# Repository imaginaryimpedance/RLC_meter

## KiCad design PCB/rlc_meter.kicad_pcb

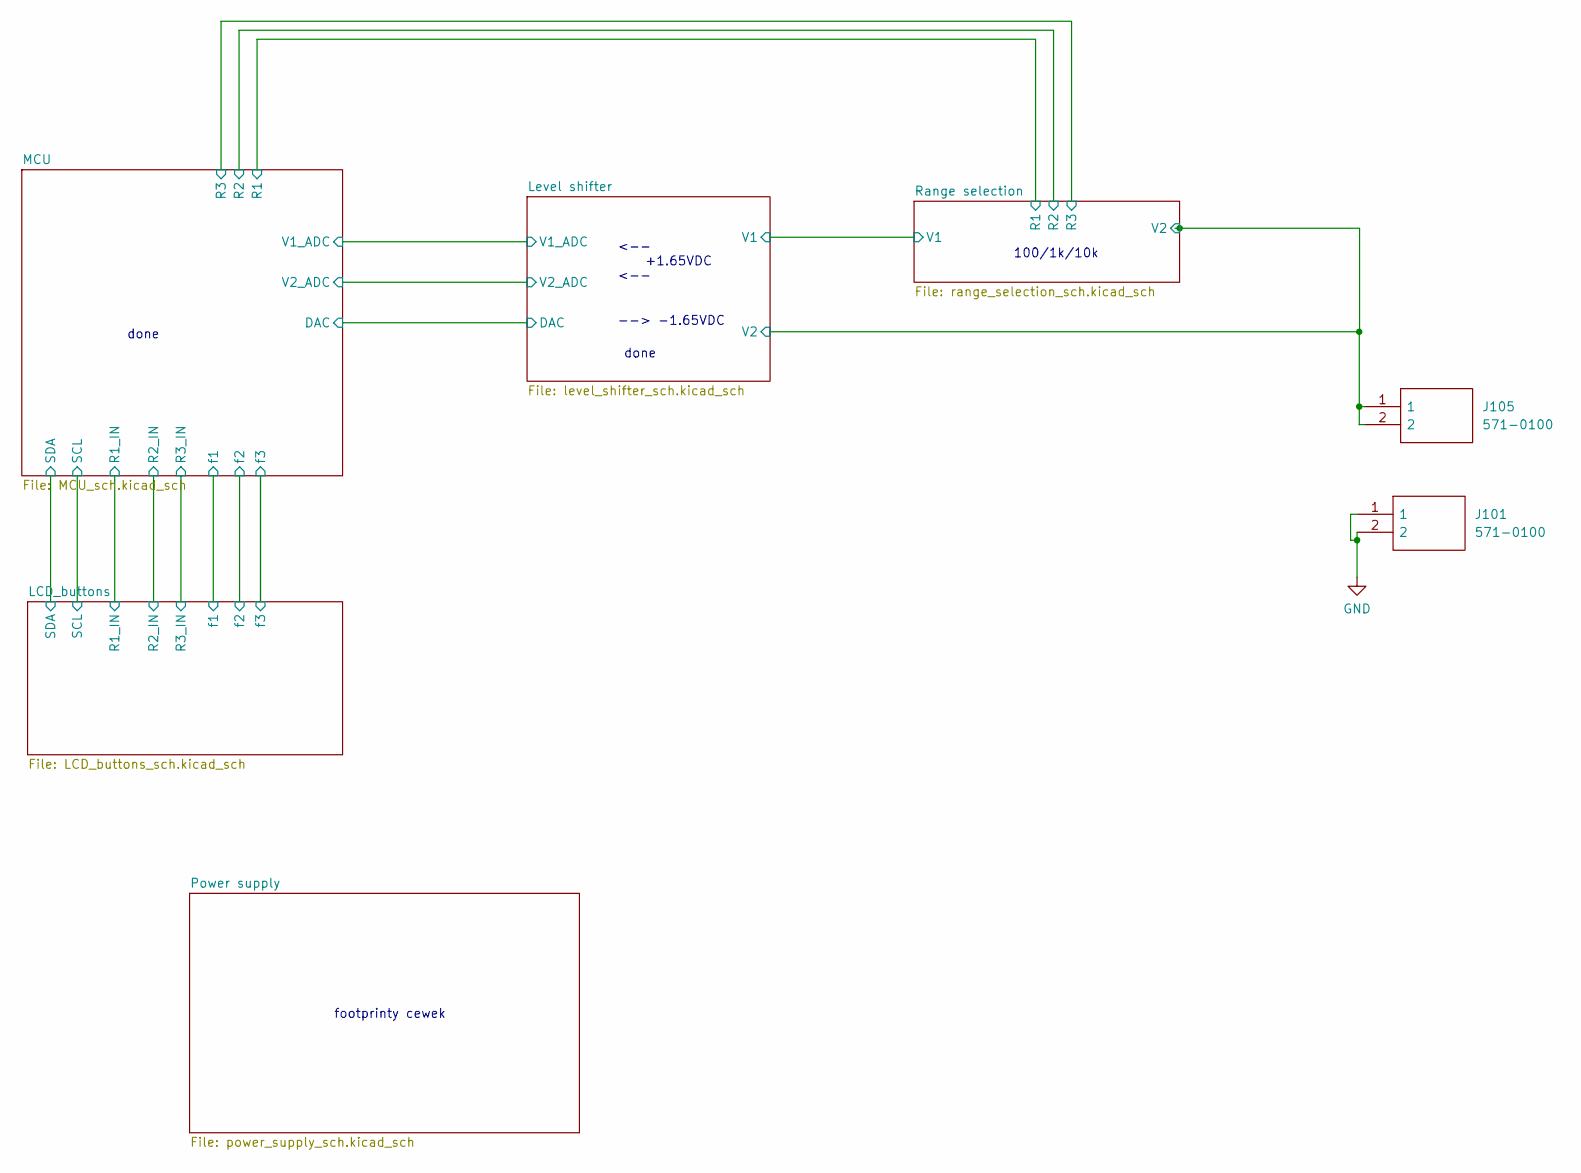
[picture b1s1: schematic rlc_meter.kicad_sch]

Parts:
J101, J105: 571-0100; 5710100; Manufacturer_Part_Number 571-0100; Mouser Part Number 164-6218

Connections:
/Level shifter/V2: J105.1, J105.2; also elsewhere on the board
GND: J101.1, J101.2; also elsewhere on the board

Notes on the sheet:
100/1k/10k
<-- +1.65VDC <--
footprinty cewek
done
--> -1.65VDC

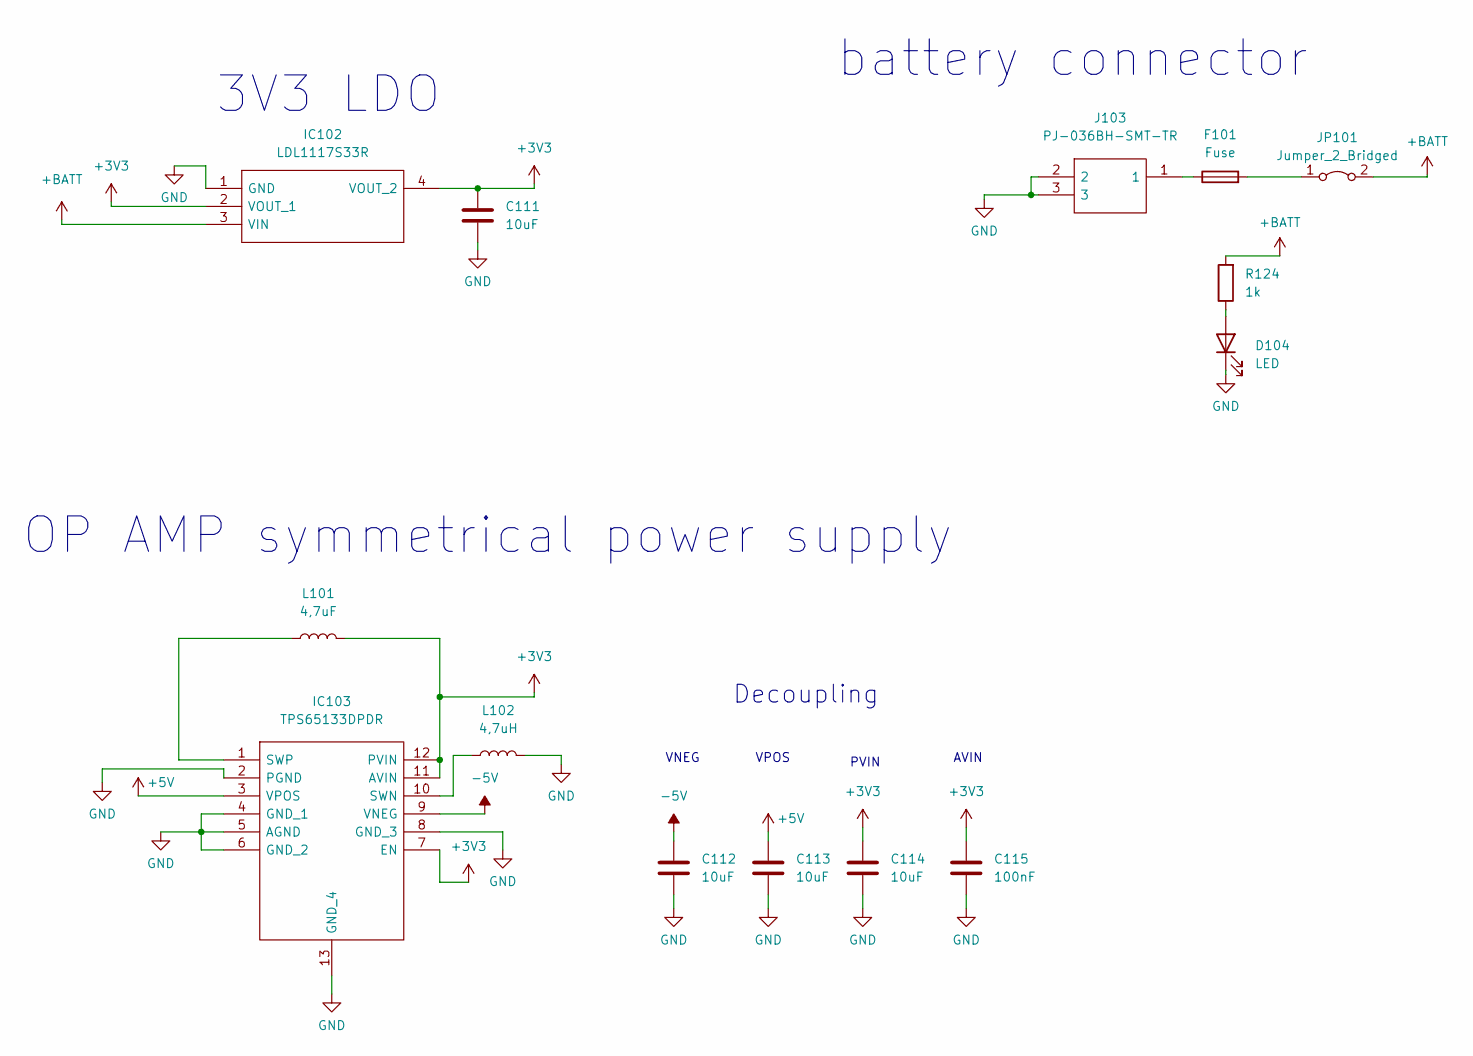
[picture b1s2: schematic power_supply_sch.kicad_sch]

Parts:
C111, C112, C113, C114: 10uF; C_1206_3216Metric
C115: 100nF; C_1206_3216Metric
D104: LED; LED_1206_3216Metric
F101: Fuse; Fuse_1206_3216Metric
IC102: LDL1117S33R; SOT230P700X180-4N; Manufacturer_Part_Number LDL1117S33R; Mouser Part Number 511-LDL1117S33R
IC103: TPS65133DPDR; SON45P300X300X80-13N-D; Manufacturer_Part_Number TPS65133DPDR; Mouser Part Number 595-TPS65133DPDR
J103: PJ-036BH-SMT-TR; PJ036BHSMTTR; Manufacturer_Part_Number PJ-036BH-SMT-TR; Mouser Part Number 490-PJ-036BH-SMT-TR
JP101: Jumper_2_Bridged; PinHeader_1x02_P2.54mm_Vertical_SMD_Pin1Right
L101: 4,7uF; 744031004
L102: 4,7uH; 744031004
R124: 1k; R_1206_3216Metric

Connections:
+3V3: C111.1, C114.1, C115.1, IC102.2 (VOUT_1), IC102.4 (VOUT_2), IC103.7 (EN), IC103.11 (AVIN), IC103.12 (PVIN), L101.2; also elsewhere on the board
+5V: C113.1, IC103.3 (VPOS); also elsewhere on the board
+BATT: IC102.3 (VIN), JP101.2 (B), R124.2
-5V: C112.1, IC103.9 (VNEG); also elsewhere on the board
GND: C111.2, C112.2, C113.2, C114.2, C115.2, D104.1 (K), IC102.1 (GND), IC103.2 (PGND), IC103.4 (GND_1), IC103.5 (AGND), IC103.6 (GND_2), IC103.8 (GND_3), IC103.13 (GND_4), J103.2, J103.3, L102.2; also elsewhere on the board
unnamed: D104.2 (A), R124.1
unnamed: F101.1, J103.1
unnamed: F101.2, JP101.1 (A)
unnamed: IC103.1 (SWP), L101.1
unnamed: IC103.10 (SWN), L102.1

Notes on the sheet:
battery connector
3V3 LDO
VPOS
PVIN
OP AMP symmetrical power supply
AVIN
Decoupling
VNEG

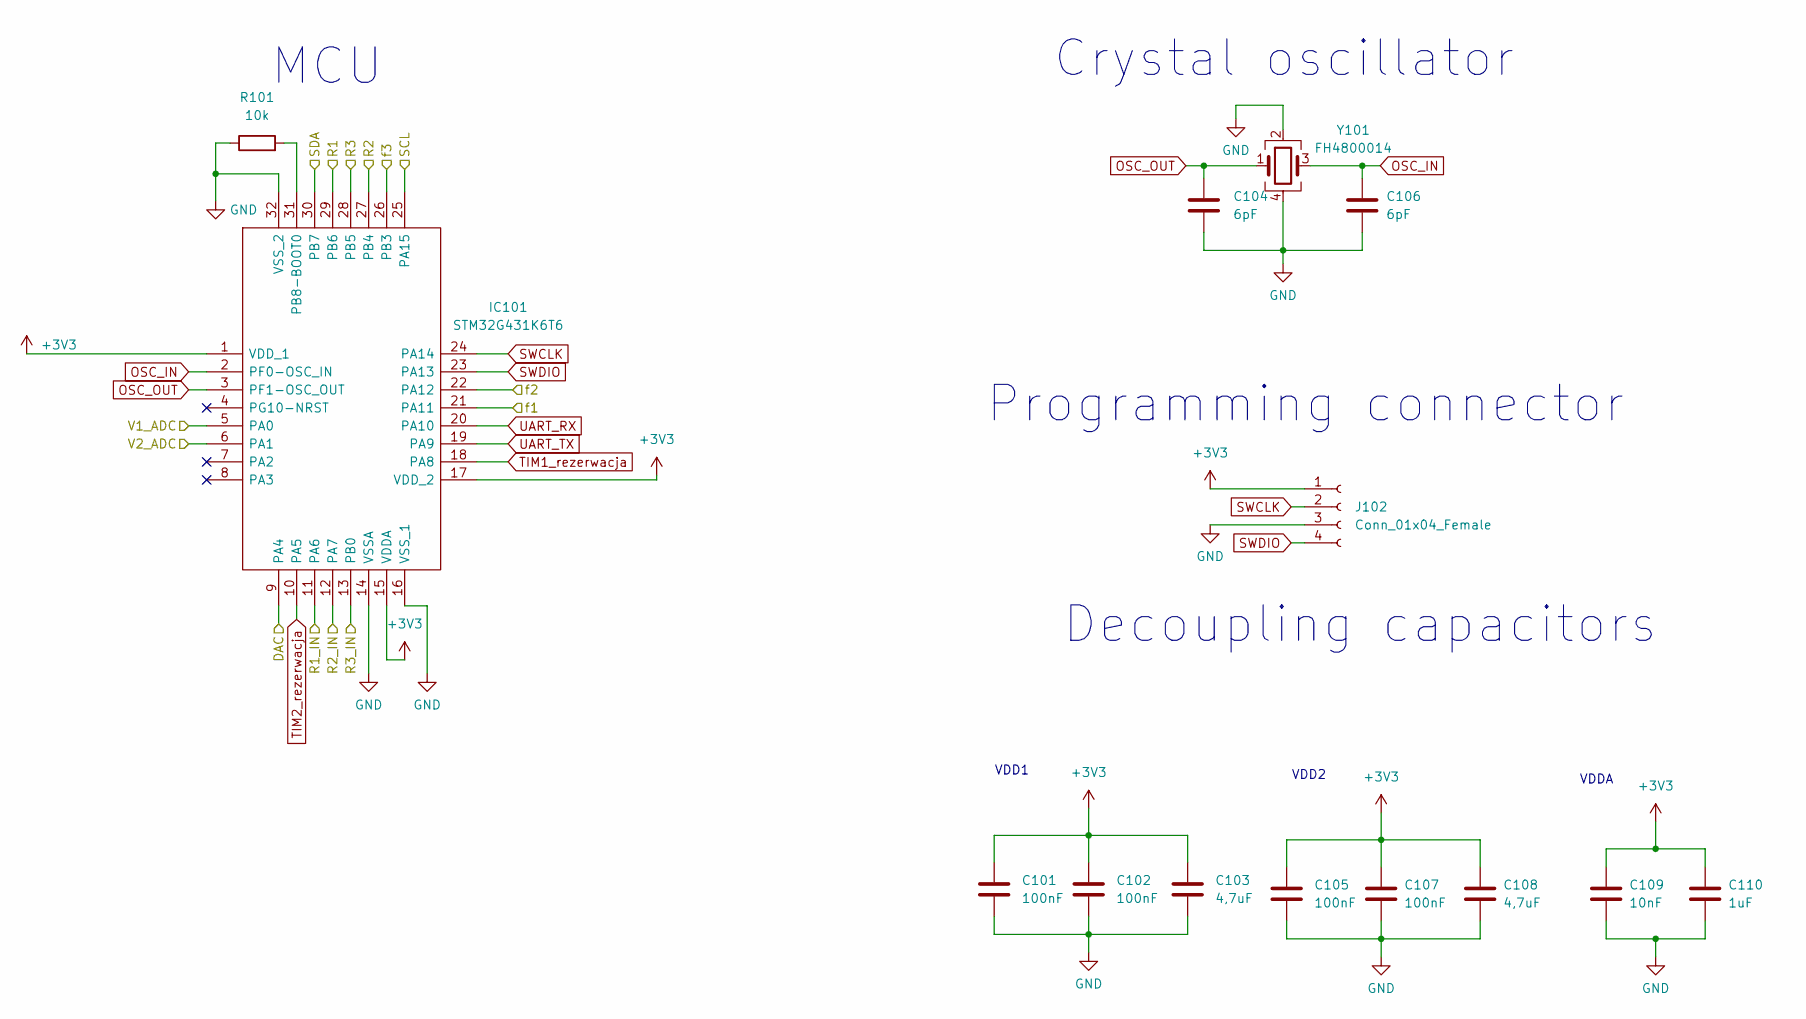
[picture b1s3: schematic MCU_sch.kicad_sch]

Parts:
C101, C102, C105, C107: 100nF; C_1206_3216Metric
C103, C108: 4,7uF; C_1206_3216Metric
C104, C106: 6pF; C_1206_3216Metric
C109: 10nF; C_1206_3216Metric
C110: 1uF; C_1206_3216Metric
IC101: STM32G431K6T6; QFP80P900X900X160-32N; Manufacturer_Part_Number STM32G431K6T6; Mouser Part Number 511-STM32G431K6T6
J102: Conn_01x04_Female; PinHeader_1x04_P2.54mm_Vertical_SMD_Pin1Left
R101: 10k; R_1206_3216Metric
Y101: FH4800014

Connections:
+3V3: C101.1, C102.1, C103.1, C105.1, C107.1, C108.1, C109.1, C110.1, IC101.1 (VDD_1), IC101.15 (VDDA), IC101.17 (VDD_2), J102.1; also elsewhere on the board
/LCD_buttons/R1_IN: IC101.11 (PA6); also elsewhere on the board
/LCD_buttons/R2_IN: IC101.12 (PA7); also elsewhere on the board
/LCD_buttons/R3_IN: IC101.13 (PB0); also elsewhere on the board
/LCD_buttons/SCL: IC101.25 (PA15); also elsewhere on the board
/LCD_buttons/SDA: IC101.30 (PB7); also elsewhere on the board
/LCD_buttons/f1: IC101.21 (PA11); also elsewhere on the board
/LCD_buttons/f2: IC101.22 (PA12); also elsewhere on the board
/LCD_buttons/f3: IC101.26 (PB3); also elsewhere on the board
/Level shifter/DAC: IC101.9 (PA4); also elsewhere on the board
/Level shifter/V1_ADC: IC101.5 (PA0); also elsewhere on the board
/Level shifter/V2_ADC: IC101.6 (PA1); also elsewhere on the board
/MCU/R1: IC101.29 (PB6); also elsewhere on the board
/MCU/R2: IC101.27 (PB4); also elsewhere on the board
/MCU/R3: IC101.28 (PB5); also elsewhere on the board
GND: C101.2, C102.2, C103.2, C104.2, C105.2, C106.2, C107.2, C108.2, C109.2, C110.2, IC101.14 (VSSA), IC101.16 (VSS_1), IC101.32 (VSS_2), J102.3, R101.1, Y101.2, Y101.4; also elsewhere on the board
unnamed: IC101.31 (PB8-BOOT0), R101.2
OSC_IN: C106.1, IC101.2 (PF0-OSC_IN), Y101.3
OSC_OUT: C104.1, IC101.3 (PF1-OSC_OUT), Y101.1
SWCLK: IC101.24 (PA14), J102.2
SWDIO: IC101.23 (PA13), J102.4
TIM1_rezerwacja: IC101.18 (PA8)
TIM2_rezerwacja: IC101.10 (PA5)
UART_RX: IC101.20 (PA10)
UART_TX: IC101.19 (PA9)

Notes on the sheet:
VDD2
MCU
VDD1
VDDA
Decoupling capacitors
Crystal oscillator
Programming connector

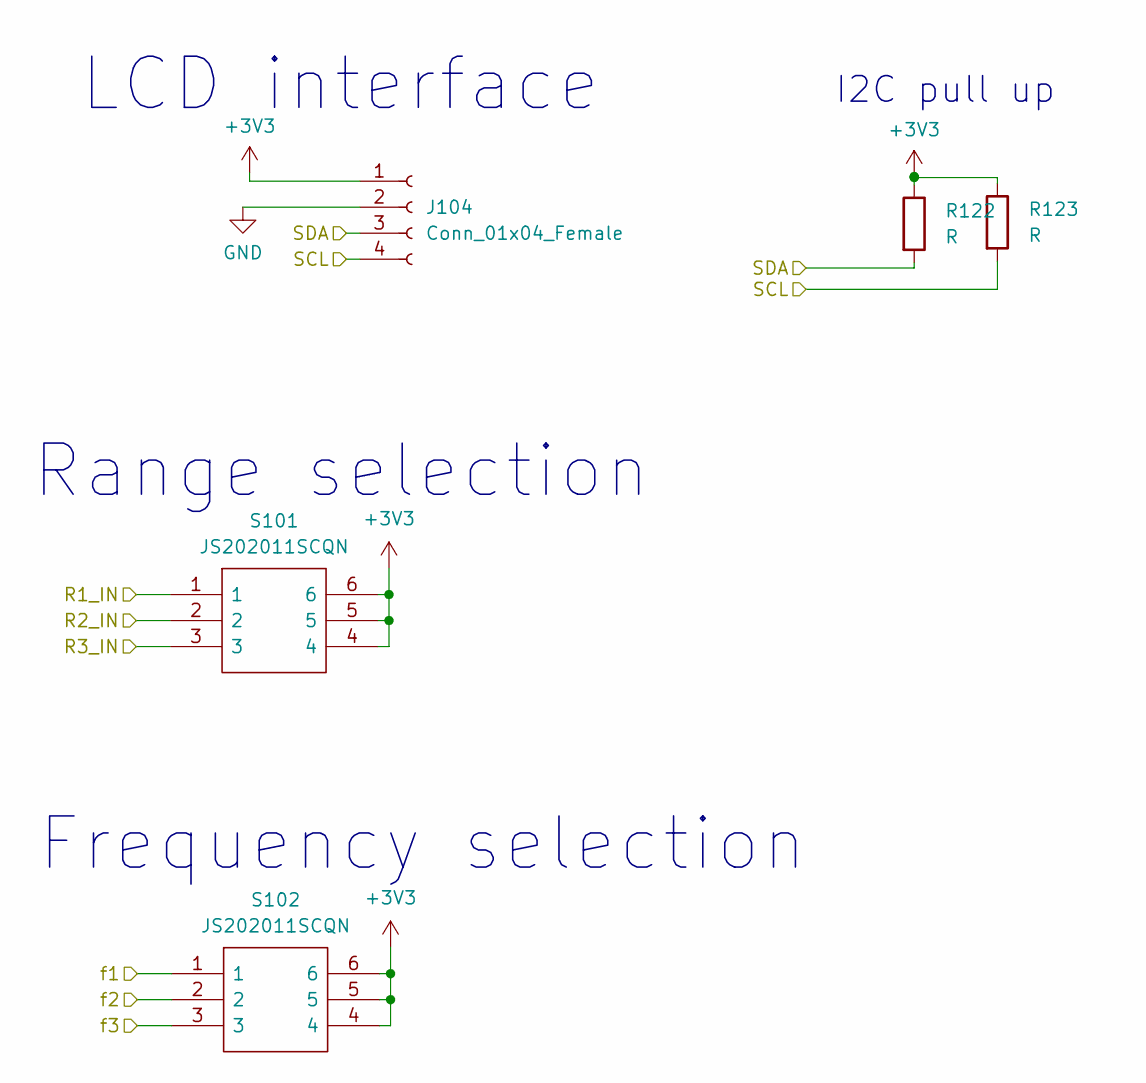
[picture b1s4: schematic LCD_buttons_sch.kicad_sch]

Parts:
J104: Conn_01x04_Female; PinHeader_1x04_P2.54mm_Vertical_SMD_Pin1Left
R122, R123: R; R_1206_3216Metric
S101, S102: JS202011SCQN; Manufacturer_Part_Number JS202011SCQN; Mouser Part Number 611-JS202011SCQN

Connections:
+3V3: J104.1, R122.1, R123.1, S101.4, S101.5, S101.6, S102.4, S102.5, S102.6; also elsewhere on the board
/LCD_buttons/R1_IN: S101.1; also elsewhere on the board
/LCD_buttons/R2_IN: S101.2; also elsewhere on the board
/LCD_buttons/R3_IN: S101.3; also elsewhere on the board
/LCD_buttons/SCL: J104.4, R123.2; also elsewhere on the board
/LCD_buttons/SDA: J104.3, R122.2; also elsewhere on the board
/LCD_buttons/f1: S102.1; also elsewhere on the board
/LCD_buttons/f2: S102.2; also elsewhere on the board
/LCD_buttons/f3: S102.3; also elsewhere on the board
GND: J104.2; also elsewhere on the board

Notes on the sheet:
I2C pull up
LCD interface
Frequency selection
Range selection

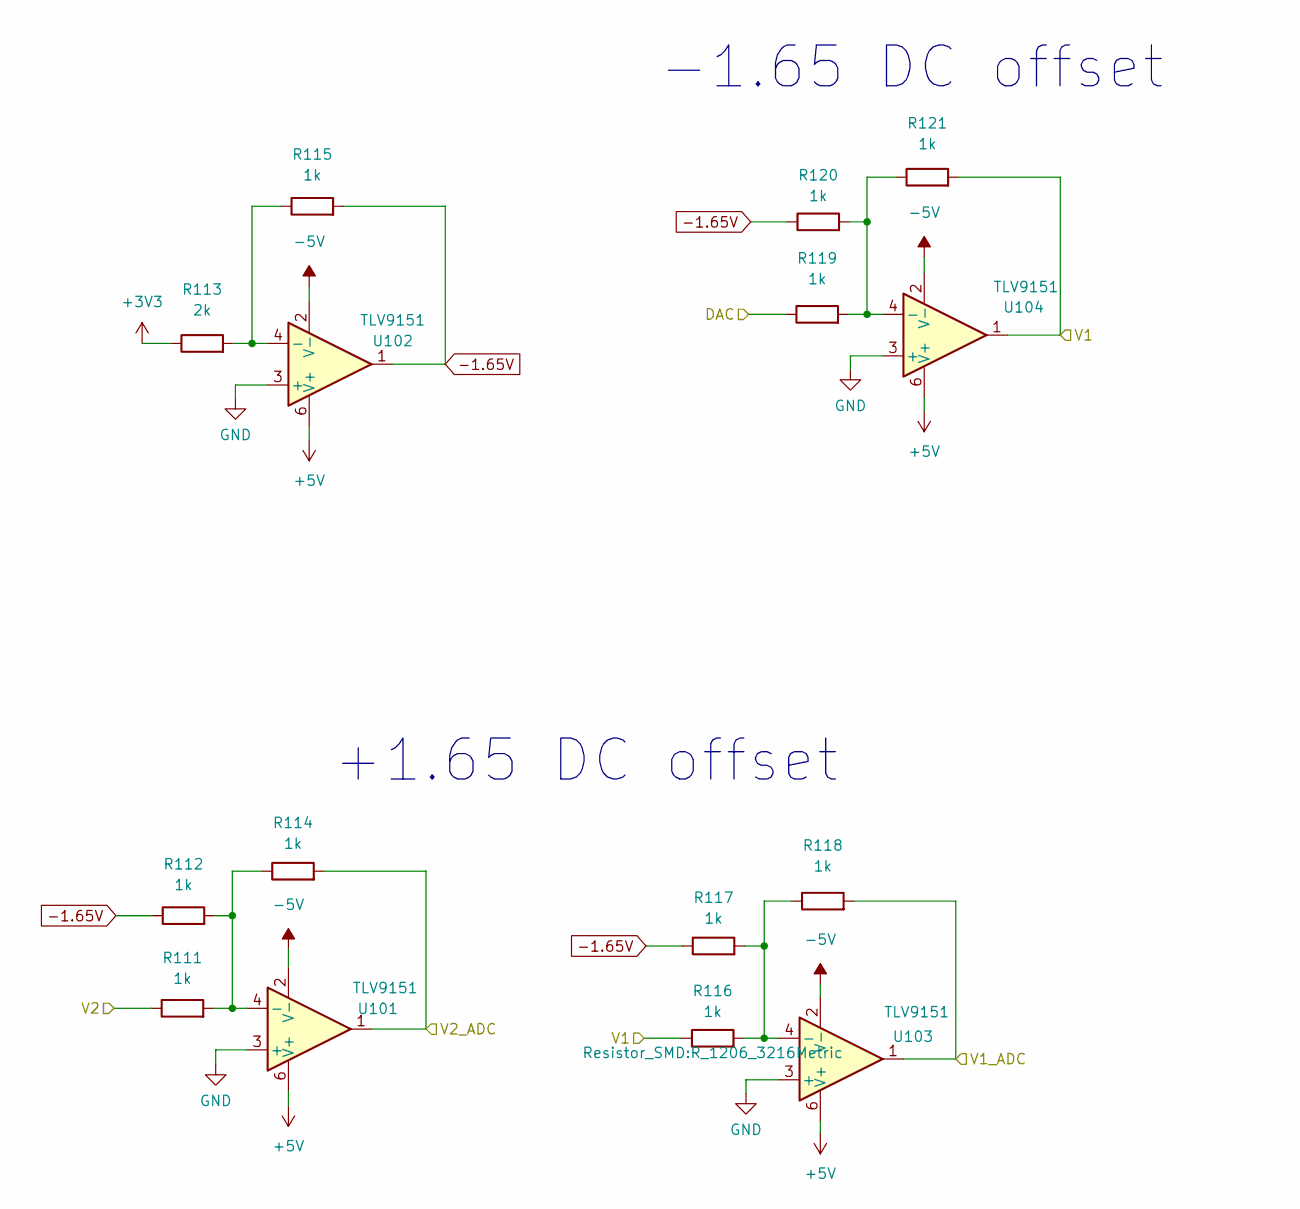
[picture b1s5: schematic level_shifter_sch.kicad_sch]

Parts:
R111, R112, R114, R115, R116, R117, R118, R119, R120, R121: 1k; R_1206_3216Metric
R113: 2k; R_1206_3216Metric
U101, U102, U103, U104: TLV9151; SOT95P280X145-6N

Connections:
+3V3: R113.1; also elsewhere on the board
+5V: U101.6 (V+), U102.6 (V+), U103.6 (V+), U104.6 (V+); also elsewhere on the board
-1.65V: R112.1, R115.2, R117.1, R120.1, U102.1
-5V: U101.2 (V-), U102.2 (V-), U103.2 (V-), U104.2 (V-); also elsewhere on the board
/Level shifter/DAC: R119.1; also elsewhere on the board
/Level shifter/V1: R116.1, R121.2, U104.1; also elsewhere on the board
/Level shifter/V1_ADC: R118.2, U103.1; also elsewhere on the board
/Level shifter/V2: R111.1; also elsewhere on the board
/Level shifter/V2_ADC: R114.2, U101.1; also elsewhere on the board
GND: U101.3 (+), U102.3 (+), U103.3 (+), U104.3 (+); also elsewhere on the board
unnamed: R111.2, R112.2, R114.1, U101.4 (-)
unnamed: R113.2, R115.1, U102.4 (-)
unnamed: R116.2, R117.2, R118.1, U103.4 (-)
unnamed: R119.2, R120.2, R121.1, U104.4 (-)

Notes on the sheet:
-1.65 DC offset
+1.65 DC offset

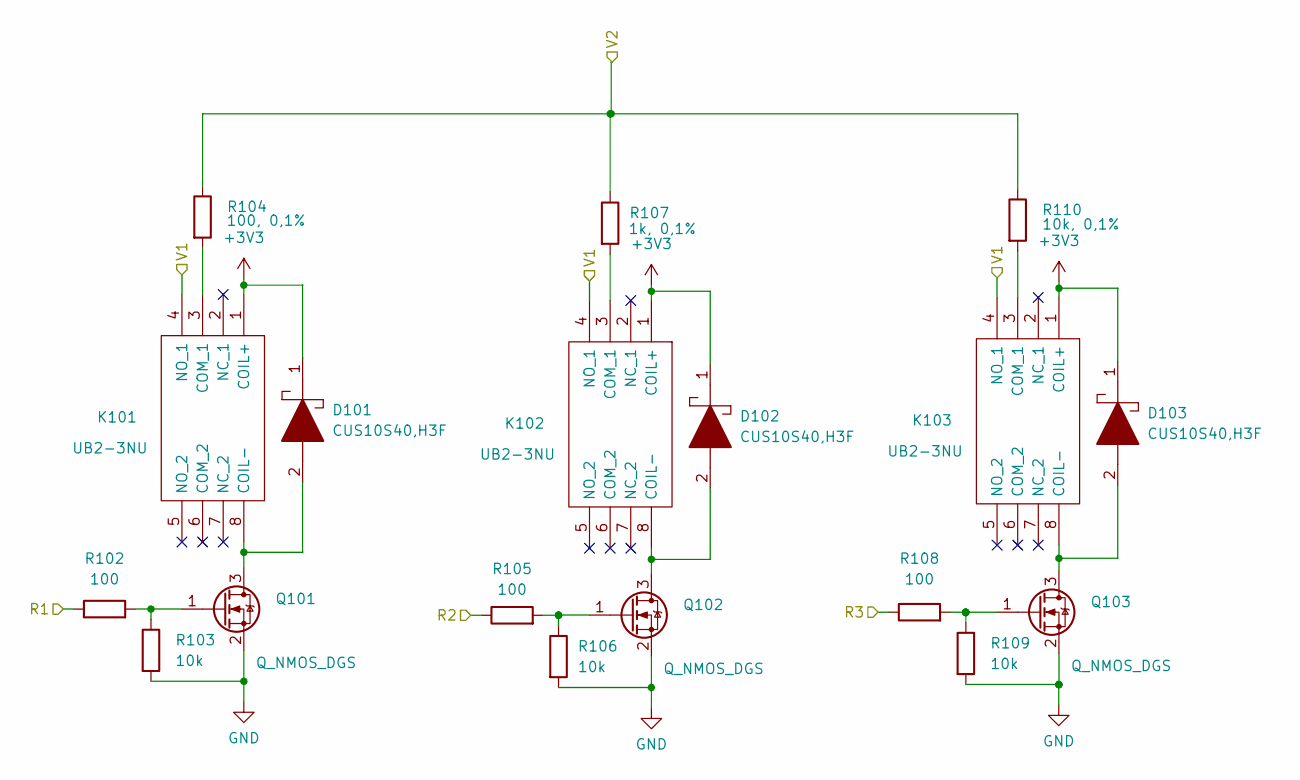
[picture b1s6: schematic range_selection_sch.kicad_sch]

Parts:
D101, D102, D103: CUS10S40,H3F; CUS10S40H3F; Manufacturer_Part_Number CUS10S40,H3F; Mouser Part Number 757-CUS10S40H3F
K101, K102, K103: UB2-3NU; UB23NU; Manufacturer_Part_Number UB2-3NU; Mouser Part Number 551-UB2-3NU
Q101, Q102, Q103: Q_NMOS_DGS; SOT96P237X111-3N
R102, R105, R108: 100; R_1206_3216Metric
R103, R106, R109: 10k; R_1206_3216Metric
R104: 100, 0,1%; R_1206_3216Metric
R107: 1k, 0,1%; R_1206_3216Metric
R110: 10k, 0,1%; R_1206_3216Metric

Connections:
+3V3: D101.1, D102.1, D103.1, K101.1 (COIL+), K102.1 (COIL+), K103.1 (COIL+); also elsewhere on the board
/Level shifter/V1: K101.4 (NO_1), K102.4 (NO_1), K103.4 (NO_1); also elsewhere on the board
/Level shifter/V2: R104.1, R107.1, R110.1; also elsewhere on the board
/MCU/R1: R102.1; also elsewhere on the board
/MCU/R2: R105.1; also elsewhere on the board
/MCU/R3: R108.1; also elsewhere on the board
GND: Q101.2 (S), Q102.2 (S), R103.2, R106.2, R109.2; also elsewhere on the board
unnamed: D101.2, K101.8 (COIL-), Q101.3 (D)
unnamed: D102.2, K102.8 (COIL-), Q102.3 (D)
unnamed: D103.2, K103.8 (COIL-), Q103.3 (D)
unnamed: K101.3 (COM_1), R104.2
unnamed: K102.3 (COM_1), R107.2
unnamed: K103.3 (COM_1), R110.2
unnamed: Q101.1 (G), R102.2, R103.1
unnamed: Q102.1 (G), R105.2, R106.1
unnamed: Q103.1 (G), R108.2, R109.1

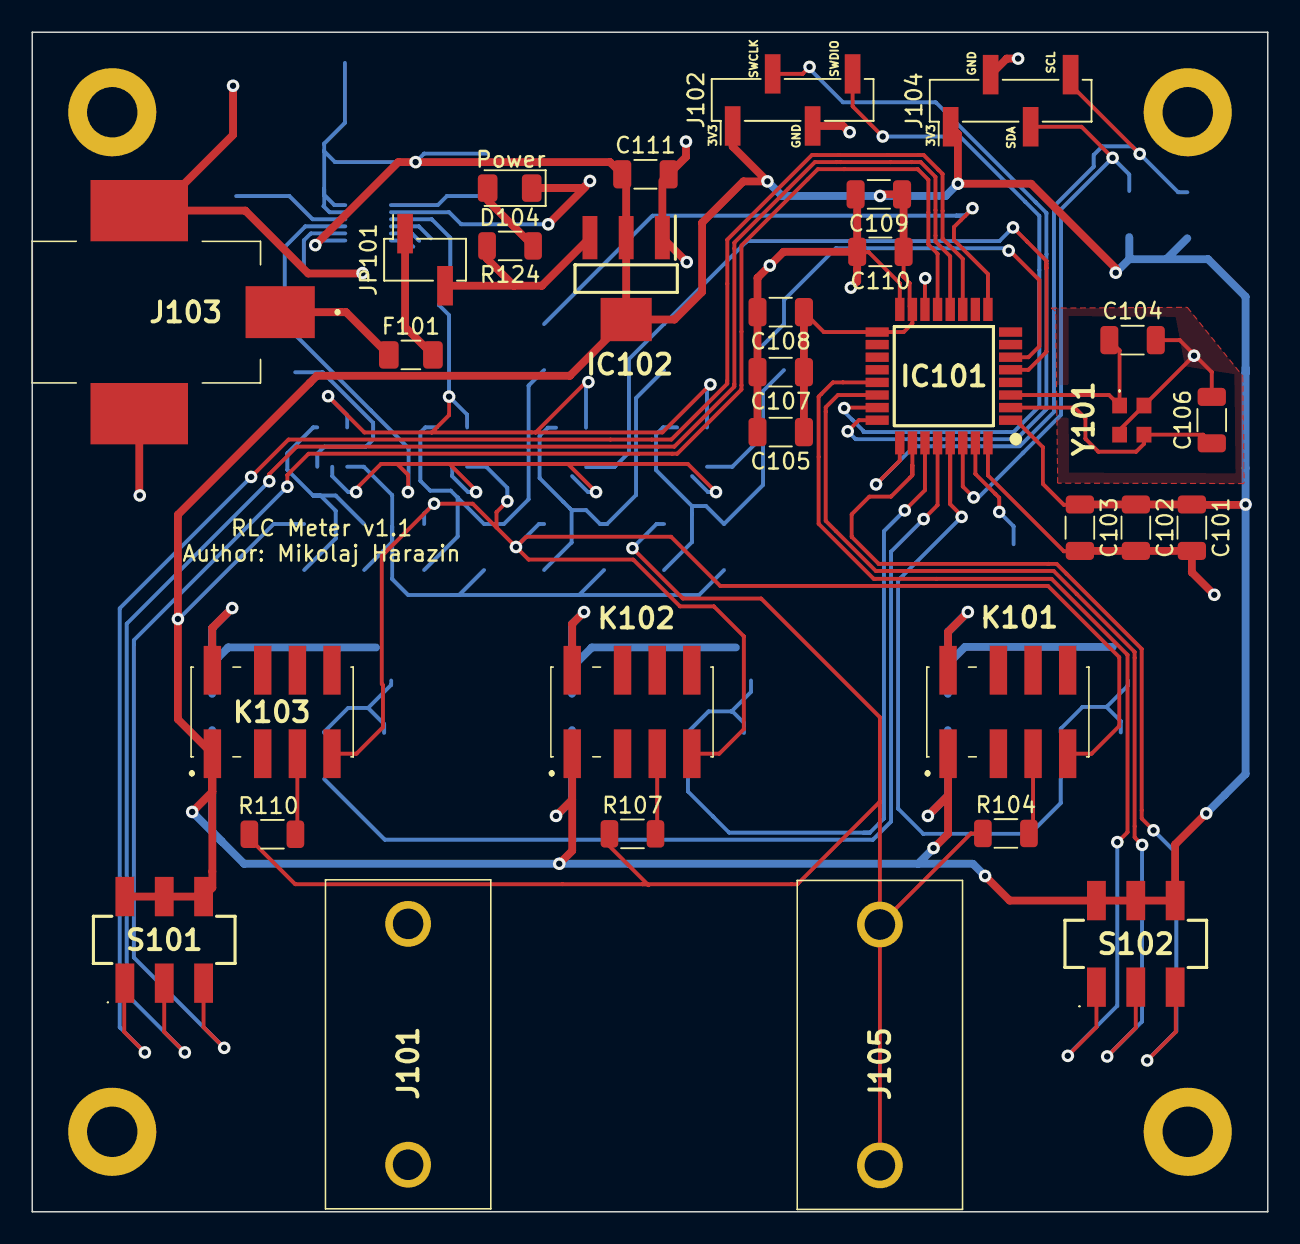
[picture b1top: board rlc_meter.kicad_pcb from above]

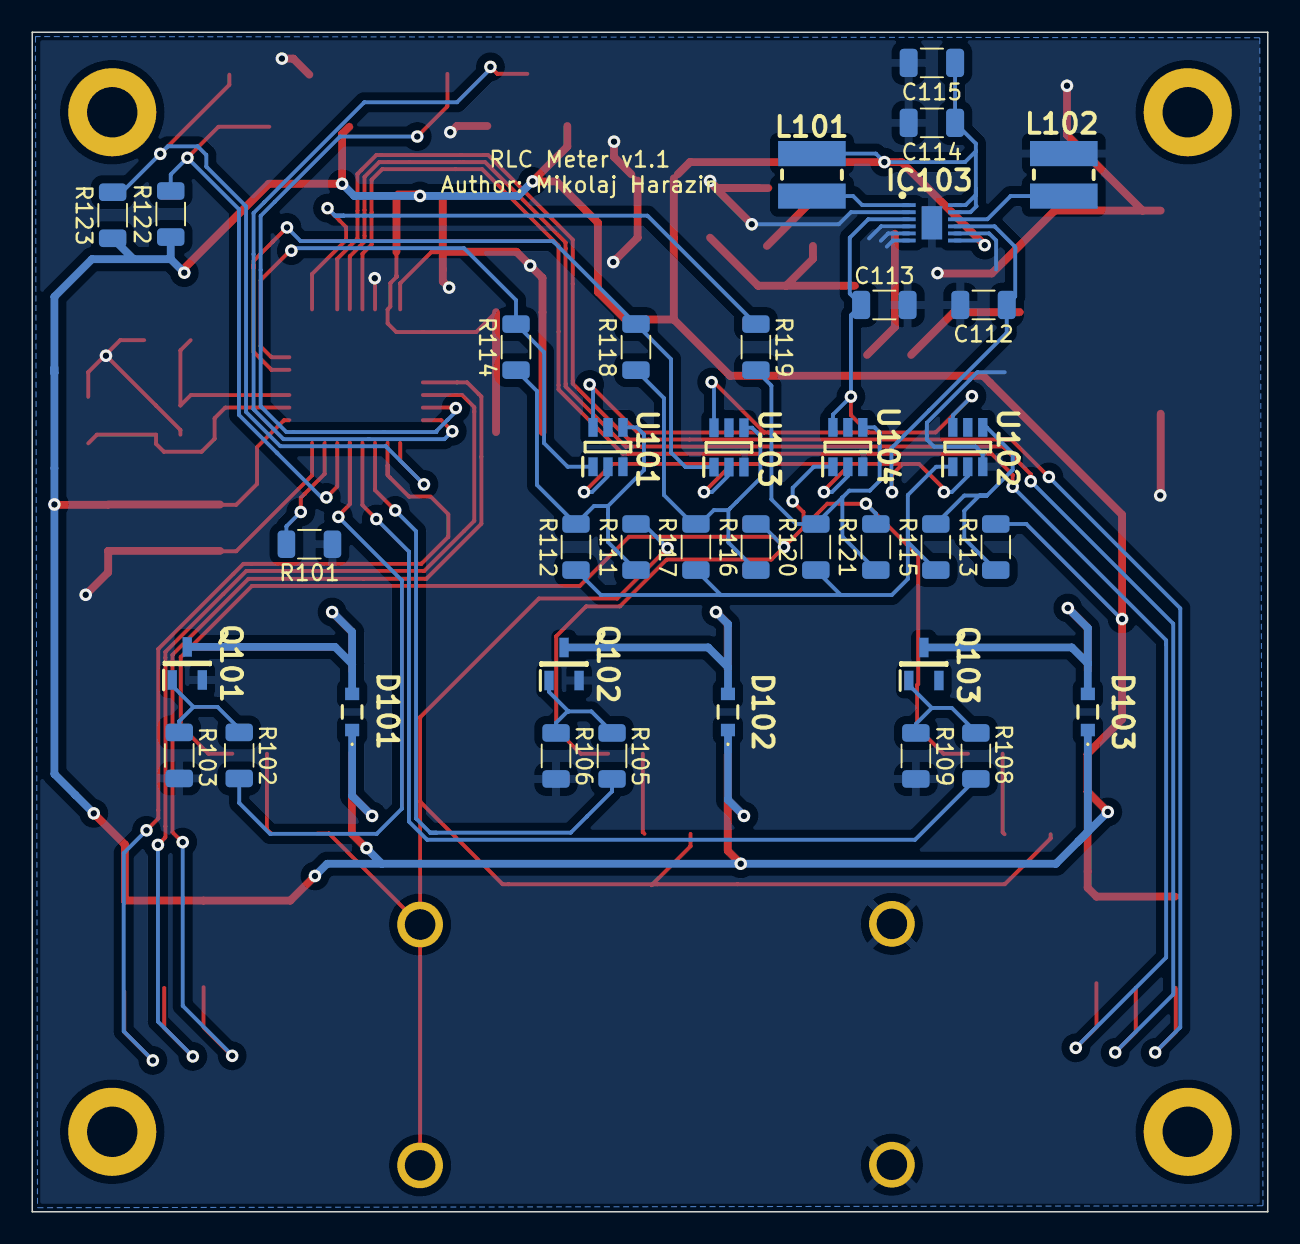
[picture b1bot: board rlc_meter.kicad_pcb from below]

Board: 2 copper layers, 78.5 x 74.9 mm, 68 parts (37 on the bottom side), 45 nets.

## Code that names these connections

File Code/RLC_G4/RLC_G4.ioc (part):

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Mcu.Name=STM32G431K(6-8-B)Tx
Mcu.Package=LQFP32
Mcu.UserName=STM32G431K6Tx
PA0.Mode=IN1-Single-Ended
PA0.Signal=ADC1_IN1
PA1.Mode=IN2-Single-Ended
PA1.Signal=ADC2_IN2
PA11.GPIOParameters=GPIO_PuPd
PA11.GPIO_PuPd=GPIO_PULLDOWN
PA11.Signal=GPIO_Input
PA12.GPIOParameters=GPIO_PuPd
PA12.GPIO_PuPd=GPIO_PULLDOWN
PA12.Signal=GPIO_Input
PA13.Signal=SYS_JTMS-SWDIO
PA14.Signal=SYS_JTCK-SWCLK
PA15.Mode=I2C
PA15.Signal=I2C1_SCL
PA5.Signal=COMP_DAC12_group
PA6.GPIOParameters=GPIO_PuPd
PA6.GPIO_PuPd=GPIO_PULLDOWN
PA6.Signal=GPIO_Input
PA7.GPIOParameters=GPIO_PuPd
PA7.GPIO_PuPd=GPIO_PULLDOWN
PA7.Signal=GPIO_Input
PB0.GPIOParameters=GPIO_PuPd
PB0.GPIO_PuPd=GPIO_PULLDOWN
PB0.Signal=GPIO_Input
PB3.GPIOParameters=GPIO_PuPd
PB3.GPIO_PuPd=GPIO_PULLDOWN
PB3.Signal=GPIO_Input
PB4.Signal=GPIO_Output
PB5.Signal=GPIO_Output
PB6.Signal=GPIO_Output
PB7.Mode=I2C
PB7.Signal=I2C1_SDA
PF0-OSC_IN.Mode=HSE-External-Oscillator
PF0-OSC_IN.Signal=RCC_OSC_IN
PF1-OSC_OUT.Mode=HSE-External-Oscillator
PF1-OSC_OUT.Signal=RCC_OSC_OUT
RCC.HSE_VALUE=48000000
RCC.SYSCLKFreq_VALUE=48000000
RCC.SYSCLKSource=RCC_SYSCLKSOURCE_HSE
board=custom

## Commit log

2023-05-07 Intial commit
